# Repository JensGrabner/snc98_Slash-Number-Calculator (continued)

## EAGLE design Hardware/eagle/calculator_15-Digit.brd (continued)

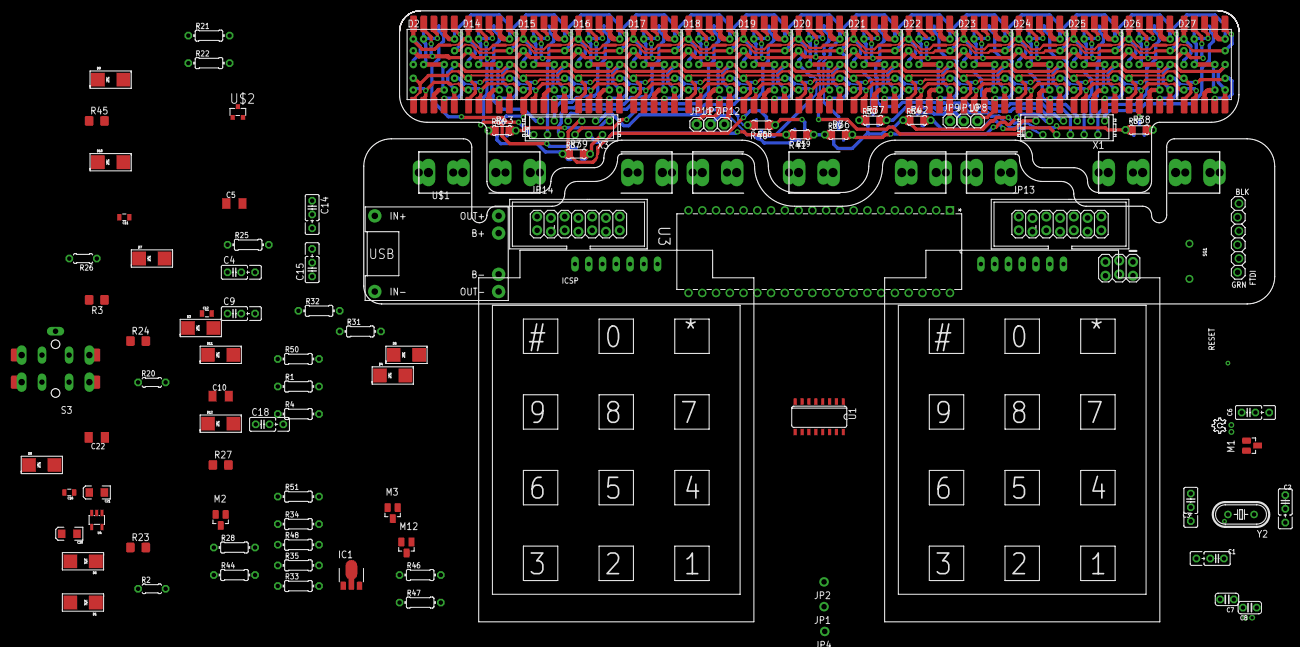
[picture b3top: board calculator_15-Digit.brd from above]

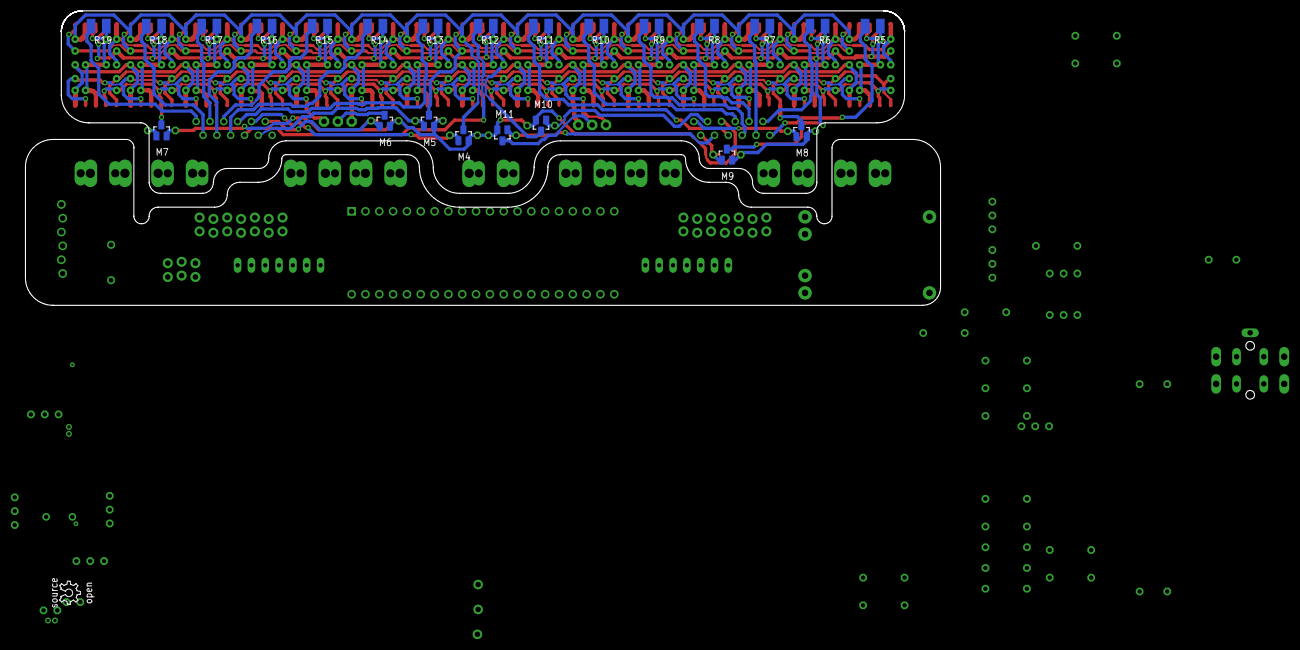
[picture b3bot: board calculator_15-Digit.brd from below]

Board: 2 copper layers, 168.1 x 54.1 mm, 151 parts (24 on the bottom side), 119 nets.
